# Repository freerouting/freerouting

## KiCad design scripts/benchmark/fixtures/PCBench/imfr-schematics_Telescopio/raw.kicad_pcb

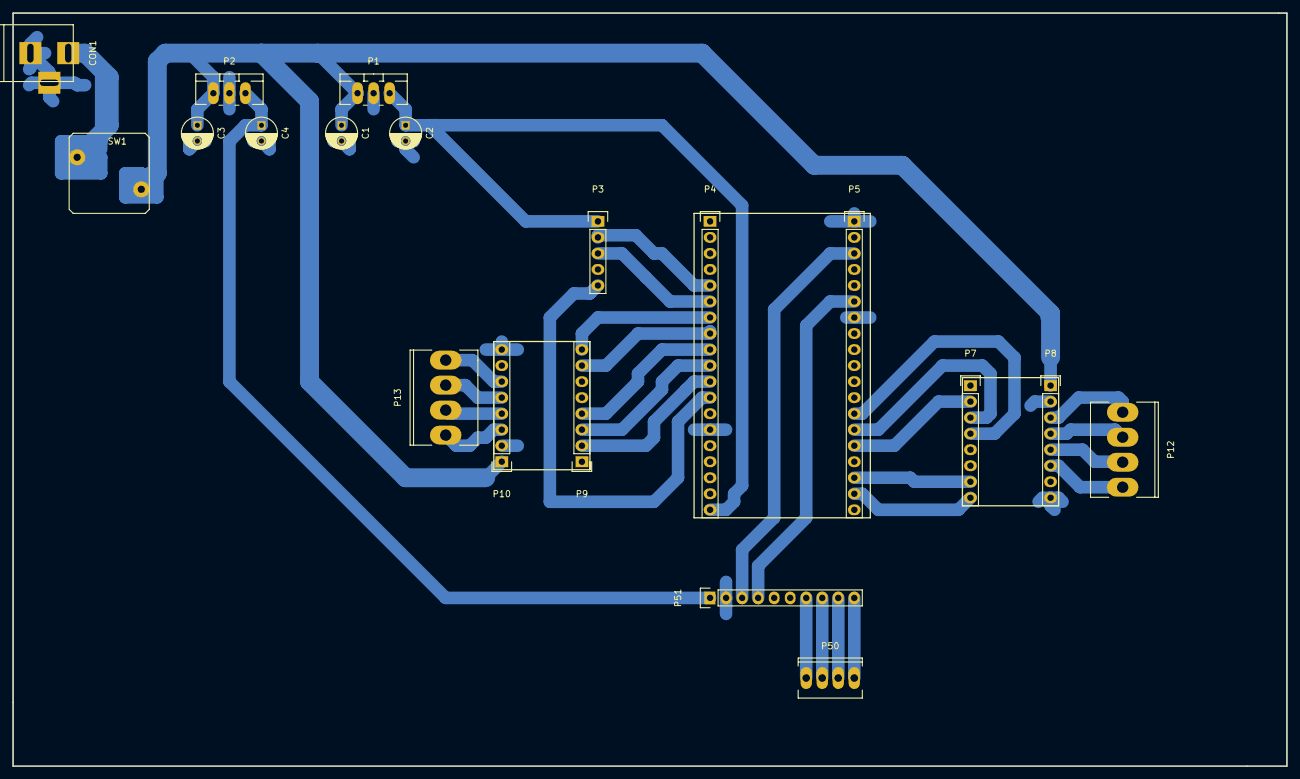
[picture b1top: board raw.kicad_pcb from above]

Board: 2 copper layers, 201.9 x 119.4 mm, 19 parts (0 on the bottom side), 32 nets.

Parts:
C1, C2, C3, C4: C; C_Radial_D5_L11_P2.5
CON1: BARREL_JACK
P1, P2: CONN_01X03; TO-220_Neutral123_Vertical_LargePads
P3: CONN_01X05; Pin_Header_Straight_1x05
P4, P5: CONN_01X19; Pin_Header_Straight_1x19
P7, P8, P9, P10: CONN_01X08; Pin_Header_Straight_1x08
P12, P13: CONN_01X04; Socket_MOLEX-KK-RM3-96mm_Lock_4pin_straight
P50: CONN_01X04; Socket_MOLEX-KK-RM2-54mm_Lock_4pin_straight
P51: CONN_01X10; Pin_Header_Straight_1x10
SW1: SW_PUSH

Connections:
/3v3: C4.1, P2.3, P51.1
/5v: C2.1, P1.3, P3.1, P4.19
/24v: CON1.1, SW1.1
/24v_Sal: C1.1, C3.1, P1.1, P2.1, P8.1, P10.1, SW1.2
/A0: P50.1, P51.7
/A1: P50.2, P51.8
/A2: P50.3, P51.9
/A3: P50.4, P51.10
/A11: P8.5, P12.3
/A12: P10.5, P13.3
/A21: P8.6, P12.4
/A22: P10.6, P13.4
/B11: P8.4, P12.2
/B12: P10.4, P13.2
/B21: P8.3, P12.1
/B22: P10.3, P13.1
/Dir_1: P5.18, P7.8
/Dir_2: P4.7, P9.8
/INT_IMU: P3.5, P4.12
/M0_1: P5.15, P7.2
/M0_2: P4.11, P9.2
/M1_1: P5.14, P7.3
/M1_2: P4.10, P9.3
/M2_1: P5.13, P7.4
/M2_2: P4.9, P9.4
/SCL: P5.3, P51.3
/SCL_2: P3.2, P4.5
/SDA: P5.6, P51.4
/SDA_2: P3.3, P4.6
/Step_1: P5.17, P7.7
/Step_2: P4.8, P9.7
GND: C1.2, C2.2, C3.2, C4.2, CON1.2, CON1.3, P1.2, P2.2, P3.4, P4.14, P5.1, P5.7, P8.2, P8.8, P10.2, P10.8, P51.2

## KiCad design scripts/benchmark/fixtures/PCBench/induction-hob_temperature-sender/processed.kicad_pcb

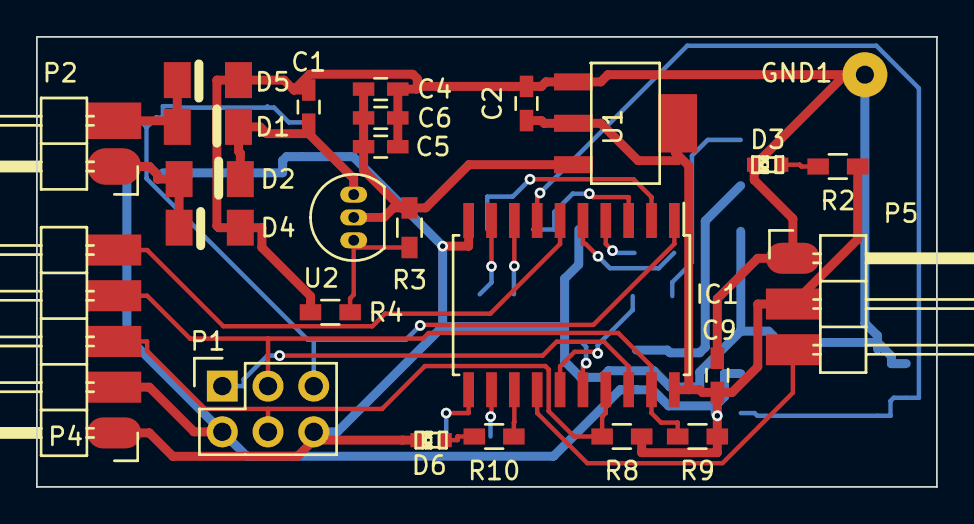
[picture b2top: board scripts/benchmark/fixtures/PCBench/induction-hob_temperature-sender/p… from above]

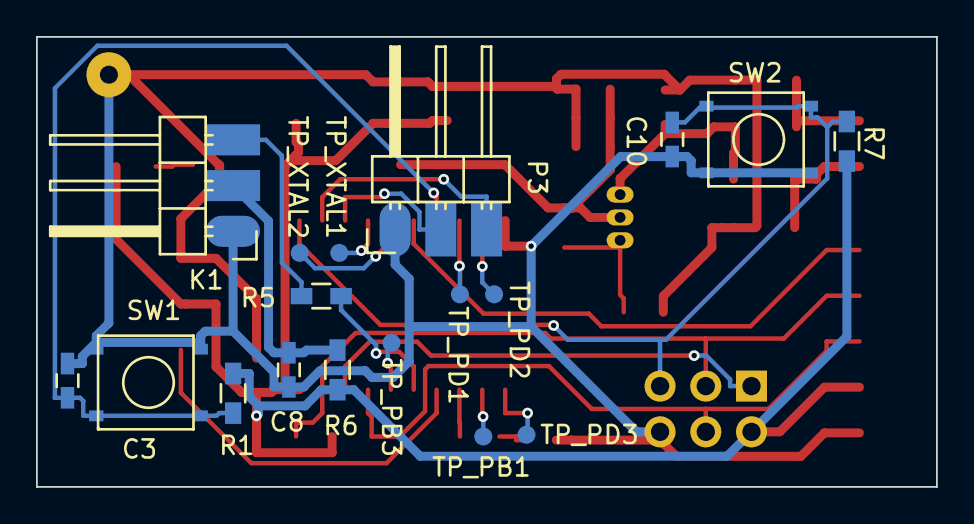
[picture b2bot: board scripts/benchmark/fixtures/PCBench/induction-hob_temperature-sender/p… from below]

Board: 2 copper layers, 50.0 x 25.0 mm, 44 parts (18 on the bottom side), 29 nets.

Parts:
C1: 1uF; C_0603_HandSoldering
C2, C4, C5, C6, C8, C9: 10uF; C_0603_HandSoldering
C3, C10: 0.1uF; C_0603_HandSoldering
D1, D2, D4, D5: D; SOD-80
D3, D6: Led_Small; LED-0603
GND1: TEST_POINT; SolderWirePad_single_1mmDrill
IC1: ATTINY2313A-S; SOIC-20_7.5x12.8mm_Pitch1.27mm
K1: SERVO; Pin_Header_Angled_SMD_1x03
P1: ISP; Socket_Strip_Straight_2x03
P2: CONN_01X02; Pin_Header_Angled_SMD_1x02
P3, P5: CONN_01X03; Pin_Header_Angled_SMD_1x03
P4: CONN_01X05; Pin_Header_Angled_SMD_1x05
R1, R7: 47k; R_0603_HandSoldering
R2, R10: 330R; R_0603_HandSoldering
R3: 240R; R_0603_HandSoldering
R4: 1k5; R_0603_HandSoldering
R5, R6: 47R; R_0603_HandSoldering
R8, R9: 5k; R_0603_HandSoldering
SW1, SW2: SW_PUSH; 4x4x1.5mm_Tactile_Push_Button_SMD
TP_PB1, TP_PB3: TEST_POINT; TP_1mm
TP_PD1, TP_PD2, TP_PD3: TEST_POINT; TP_1mm
TP_XTAL1, TP_XTAL2: TEST_POINT; TP_1mm
U1: AMS1117; SOT-223
U2: LM317L; TO-92_Inline_Narrow_Oval

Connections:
+3V3: C2.1, C9.1, IC1.20, P1.2, P4.2, P5.2, R1.1, R2.1, R6.2, R7.1, R8.1, R9.1, U1.2, U1.4
/9v: C4.1, C5.1, C6.1, R3.2, U1.3, U2.2
/ALERT: IC1.6, P4.5
/MISO: IC1.18, P1.1
/RESET: C10.1, IC1.1, P1.5, R7.2, SW2.2
/RF_DATA: IC1.14, P5.3
/RX: IC1.2, P3.3
/SCL: IC1.19, P1.3, P4.4, R9.2
/SDA/MOSI: IC1.17, P1.4, P4.3, R8.2
/SERVO1: IC1.15, R5.2
/SERVO_PWR: C8.1, K1.2, R6.1
/SERVO_SIG: K1.3, R5.1
/SW: C3.2, IC1.7, R1.2, SW1.1
/TX: IC1.3, P3.2
/Vadj: R3.1, R4.2, U2.1
/Vin1: D1.2, D5.1, P2.2
/Vin2: D2.2, D4.1, P2.1
/Vin_rec: C1.1, D1.1, D2.1, U2.3
GND: C1.2, C2.2, C3.1, C4.2, C5.2, C6.2, C8.2, C9.2, C10.2, D3.1, D4.2, D5.2, D6.1, GND1.1, IC1.10, K1.1, P1.6, P3.1, P4.1, P5.1, R4.1, SW1.2, SW2.1, U1.1
unnamed: D3.2, R2.2
unnamed: D6.2, R10.2
unnamed: IC1.4, TP_XTAL1.1
unnamed: IC1.5, TP_XTAL2.1
unnamed: IC1.8, TP_PD1.1
unnamed: IC1.9, TP_PD2.1
unnamed: IC1.11, TP_PD3.1
unnamed: IC1.12, TP_PB1.1
unnamed: IC1.13, R10.1
unnamed: IC1.16, TP_PB3.1

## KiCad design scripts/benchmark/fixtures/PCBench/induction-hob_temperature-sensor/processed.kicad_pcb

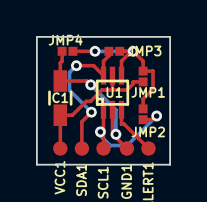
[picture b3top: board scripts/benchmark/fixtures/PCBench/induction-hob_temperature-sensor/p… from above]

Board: 2 copper layers, 7.4 x 7.1 mm, 11 parts (0 on the bottom side), 6 nets.

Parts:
ALERT1: TEST_POINT; SMD_TP0.8mm
C1: C; C_0603_HandSoldering
GND1: TEST_POINT; SMD_TP0.8mm
JMP1, JMP2, JMP3, JMP4: R; SOLDER_JUMPER
SCL1: TEST_POINT; SMD_TP0.8mm
SDA1: TEST_POINT; SMD_TP0.8mm
U1: TMP102; SOT563
VCC1: TEST_POINT; SMD_TP0.8mm

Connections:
/ADD0: JMP1.2, JMP2.2, JMP3.2, JMP4.1, U1.4
/ALERT: ALERT1.1, U1.3
/SCL: JMP2.1, SCL1.1, U1.1
/SDA: JMP3.1, SDA1.1, U1.6
/VCC: C1.1, JMP1.1, U1.5, VCC1.1
GND: C1.2, GND1.1, JMP4.2, U1.2
